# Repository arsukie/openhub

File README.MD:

# OpenHub

An open-source USB 2.0 hub. USB-C in, 4 ports out (2x USB-C, 2x USB-A)

> schematic's done, PCB is routed, board's off to fab. what could go wrong

## What it is

- USB 2.0 High-Speed (480 Mbps), running on a CoreChips **SL2.1A** hub controller (SOP-16)
- USB-C upstream (USBC1) - configured as a **sink** via 5.1kΩ CC pull-downs (Rd), so it correctly IDs as a device drawing power
- 2x USB-C downstream (USBC2, USBC3) - configured as **sources** via 56kΩ CC pull-ups (Rp), advertising default USB power out
- 2x USB-A downstream, wired straight off the controller's remaining data channels
- **SY6280AAC** current-limited power switch (U1) on the power path, current limit set via a 4.7kΩ ISET resistor (R8) - so a bad downstream device doesn't take the whole hub down with it
- EN pin on the power switch tied directly to VBUS, so downstream power just turns on the moment the hub gets plugged in, no extra logic needed
- Status LED with a 1kΩ series resistor because a silent hub is a suspicious hub
- 12MHz crystal + 15pF load caps for the controller clock
- 10µF / 100nF decoupling pairs at every rail (VDD18/VDD33/VDD5) and at each port, because unstable rails are how you get a board that works on your desk and nowhere else

## Status
Schematic + routing: done.

# Bill of Materials
 
## Selected Parts (12 items)
 
| Part Detail | Selected by | Top Designator | Qty | Source | Ext. Price |
|---|---|---|---|---|---|
| CL21A106KAYNNNE (Basic, C15850) | System | C10,C11,C12,C13... | 10 | JLCPCB | $0.9600 |
| TYPE-C-31-M-12 (Extended, C165948) | System | USBC1,USBC2,USB... | 6 | JLCPCB | $1.1136 |
| SL2.1A (Extended, C6798314) | Customer | U2 | 2 | JLCPCB | $0.5086 |
| 0603WAF5101T5E (Basic, C23186) | System | R1,R2 | 4 | JLCPCB | $0.0100 |
| CL10A106MA8NRNC (Basic, C96446) | System | C1,C2 | 4 | JLCPCB | $0.3168 |
| SY6280AAC (Extended, C55136) | System | U1 | 5 | JLCPCB | $0.4795 |
| HoLTT0603-1/10W-4.7K-1% (Extended, C2904521) | System | R8 | 6 | JLCPCB | $0.2310 |
| USB-231-ARY (Extended, C720525) | System | USB1,USB2 | 4 | JLCPCB | $0.7768 |
| A-SP192DGHC-C01-4T (Extended, C19171301) | System | LED1 | 20 | JLCPCB | $0.5600 |
| CC0603KRX7R9BB104 (Basic, C14663) | System | C5,C6,C7,C8,C9,... | 14 | JLCPCB | $0.2100 |
| RC0805FR-071KL (Extended, C95781) | System | R7 | 20 | JLCPCB | $0.1140 |
| CL10C150JB8NNNC (Basic, C1644) | System | C3,C4 | 4 | JLCPCB | $0.0556 |
 
## PCB & Shipping
 
| Type | Item | Description | Qty | Build Time | Price |
|---|---|---|---|---|---|
| PCB | Gerber_PCB1_2026-08-09_Y6 | PCB prototype: Y6-13163216A, Black, 1.6 Thickness, HASL(with lead) | 5 pcs | 24 hours | $4.00 |
| PCBA | Gerber_PCB1_2026-08-09_Y6 | Economic PCBA: SMT026080960460-13163216A, Assemble top side | 2 pcs | 2 - 3 days | $39.07 |
| PCB | Gerber_PCB1_2026-08-16_Y8 | PCB prototype: Y8-13163216A, Green, 1.6 Thickness, HASL(with lead) | 5 pcs | 3 - 4 days | $7.00 |
 
| | |
|---|---|
| **PCB (Merchandise)** | $50.07 |
| Shipping | $18.21 |
| **Subtotal** | **$68.28** |

## Cart

## Milestones

1. Design finalization - schematic + routing done

Built by **Arjun Khanal** @aruskie

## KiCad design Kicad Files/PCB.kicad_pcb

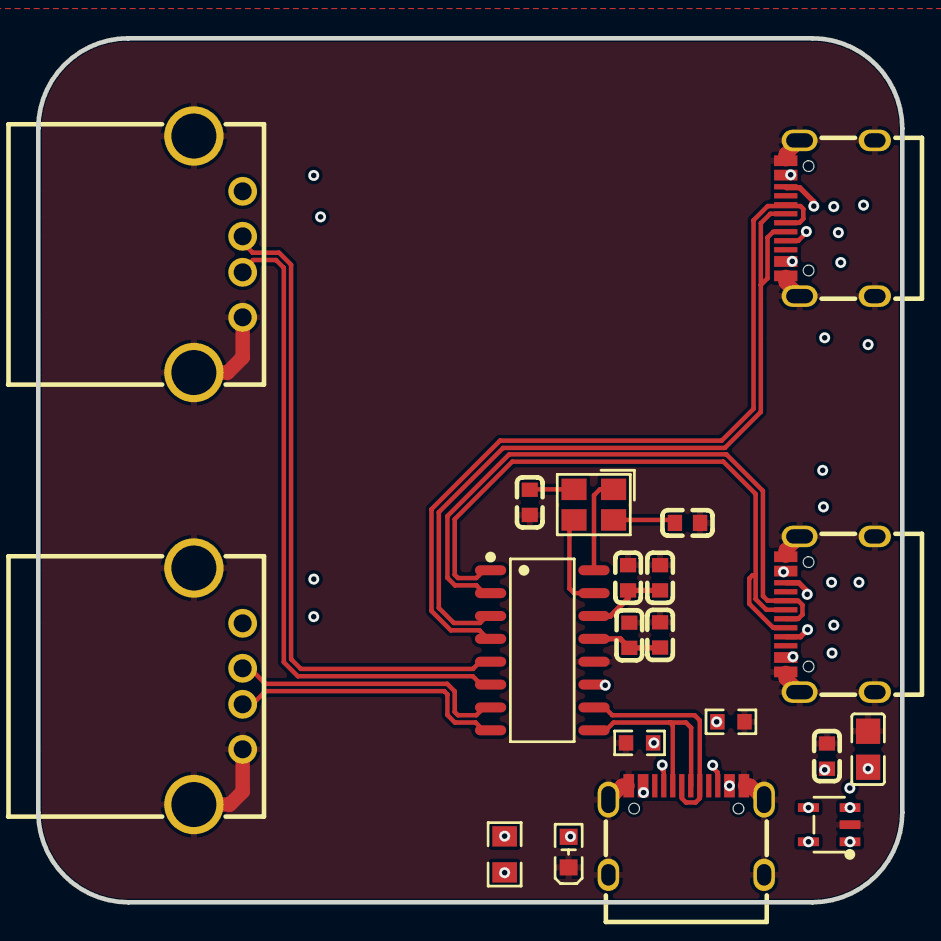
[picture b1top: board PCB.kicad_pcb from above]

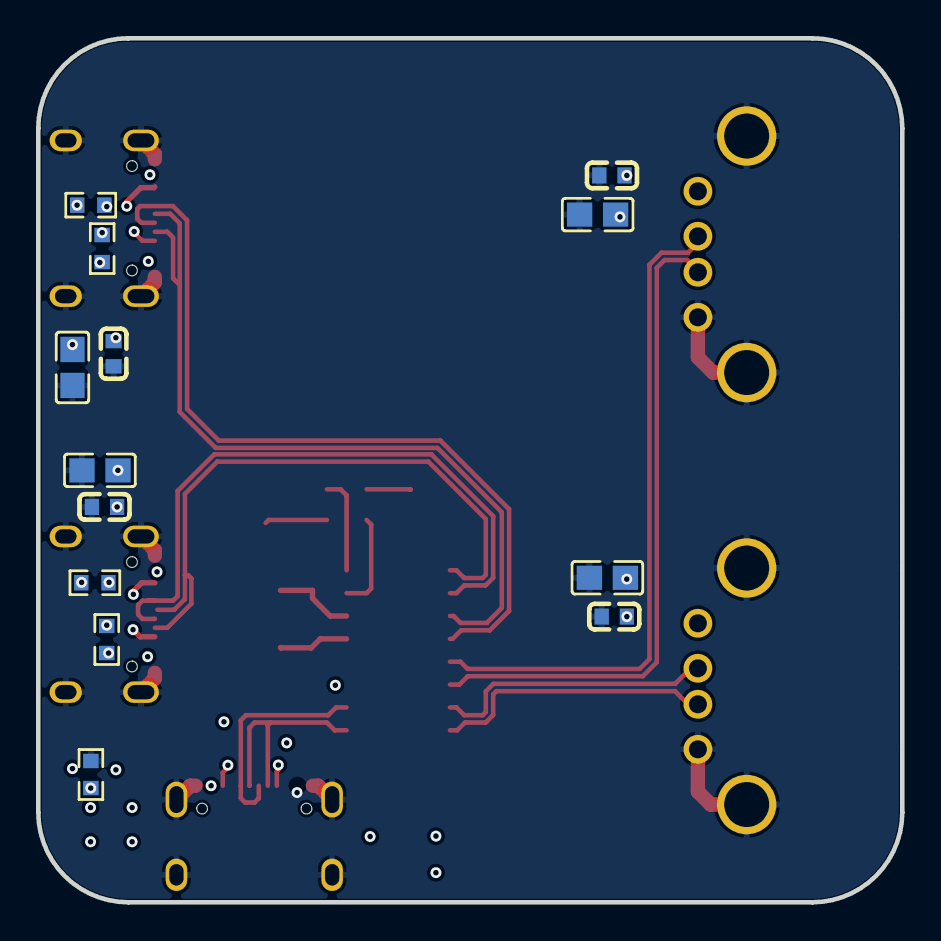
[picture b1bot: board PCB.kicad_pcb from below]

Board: 4 copper layers, 48.0 x 48.0 mm, 33 parts (13 on the bottom side), 27 nets.

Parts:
C1, C2, C3, C4, C5, C6, C7, C8, C9, C15, C16: C0603
C10, C11, C12, C13, C14: C0805
LED1: LED0603-FD
R1, R2, R3, R4, R5, R6, R8: R0603
R7: R0805
U1: SOT-23-5_L3.0-W1.7-P0.95-LS2.8-BL
U2: SOP-16_L10.0-W3.9-P1.27-LS6.0-BL
USB1, USB2: USB-A-TH_USB-231-ARY
USBC1, USBC2, USBC3: USB-C_SMD-TYPE-C-31-M-12_1
X1: CRYSTAL-SMD_4P-L3.2-W2.5-BL

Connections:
$1N151: C1.1, C16.2, U2.14
$1N152: C2.1, C15.2, U2.13
$1N156: U2.15, X1.3
$1N157: U2.16, X1.1
$1N158: C4.1, X1.4
$1N159: C3.2, X1.2
$1N181: R1.2, USBC1.A5
$1N182: R2.1, USBC1.B5
$1N206: R4.2, USBC2.B5
$1N207: R3.2, USBC2.A5
$1N223: R6.2, USBC3.B5
$1N224: R5.2, USBC3.A5
$1N239: LED1.1, R7.2
$1N246: U1.4, U1.5, USBC1.A4B9, USBC1.B4A9
$1N248: R8.1, U1.3
+5V: C5.1, C6.1, C7.2, C8.2, C9.2, C10.2, C11.2, C12.2, C13.1, C14.1, R3.1, R4.1, R5.1, R6.1, R7.1, U1.1, U2.11, USB1.1, USB2.1, USBC2.A4B9, USBC2.B4A9, USBC3.A4B9, USBC3.B4A9
D+: U2.10, USBC1.A6, USBC1.B6
D-: U2.9, USBC1.A7, USBC1.B7
DM1: U2.7, USB1.2
DM2: U2.5, USB2.2
DM3: U2.3, USBC2.A7, USBC2.B7
DM4: U2.1, USBC3.A7, USBC3.B7
DP1: U2.8, USB1.3
DP2: U2.6, USB2.3
DP3: U2.4, USBC2.A6, USBC2.B6
DP4: U2.2, USBC3.A6, USBC3.B6
GND: C1.2, C2.2, C3.1, C4.2, C5.2, C6.2, C7.1, C8.1, C9.1, C10.1, C11.1, C12.1, C13.2, C14.2, C15.1, C16.1, LED1.2, R1.1, R2.2, R8.2, U1.2, U2.12, USB1.4, USB1.5, USB1.6, USB2.4, USB2.5, USB2.6, USBC1.1, USBC1.2, USBC1.3, USBC1.4, USBC1.A1B12, USBC1.B1A12, USBC2.1, USBC2.2, USBC2.3, USBC2.4, USBC2.A1B12, USBC2.B1A12, USBC3.1, USBC3.2, USBC3.3, USBC3.4, USBC3.A1B12, USBC3.B1A12
